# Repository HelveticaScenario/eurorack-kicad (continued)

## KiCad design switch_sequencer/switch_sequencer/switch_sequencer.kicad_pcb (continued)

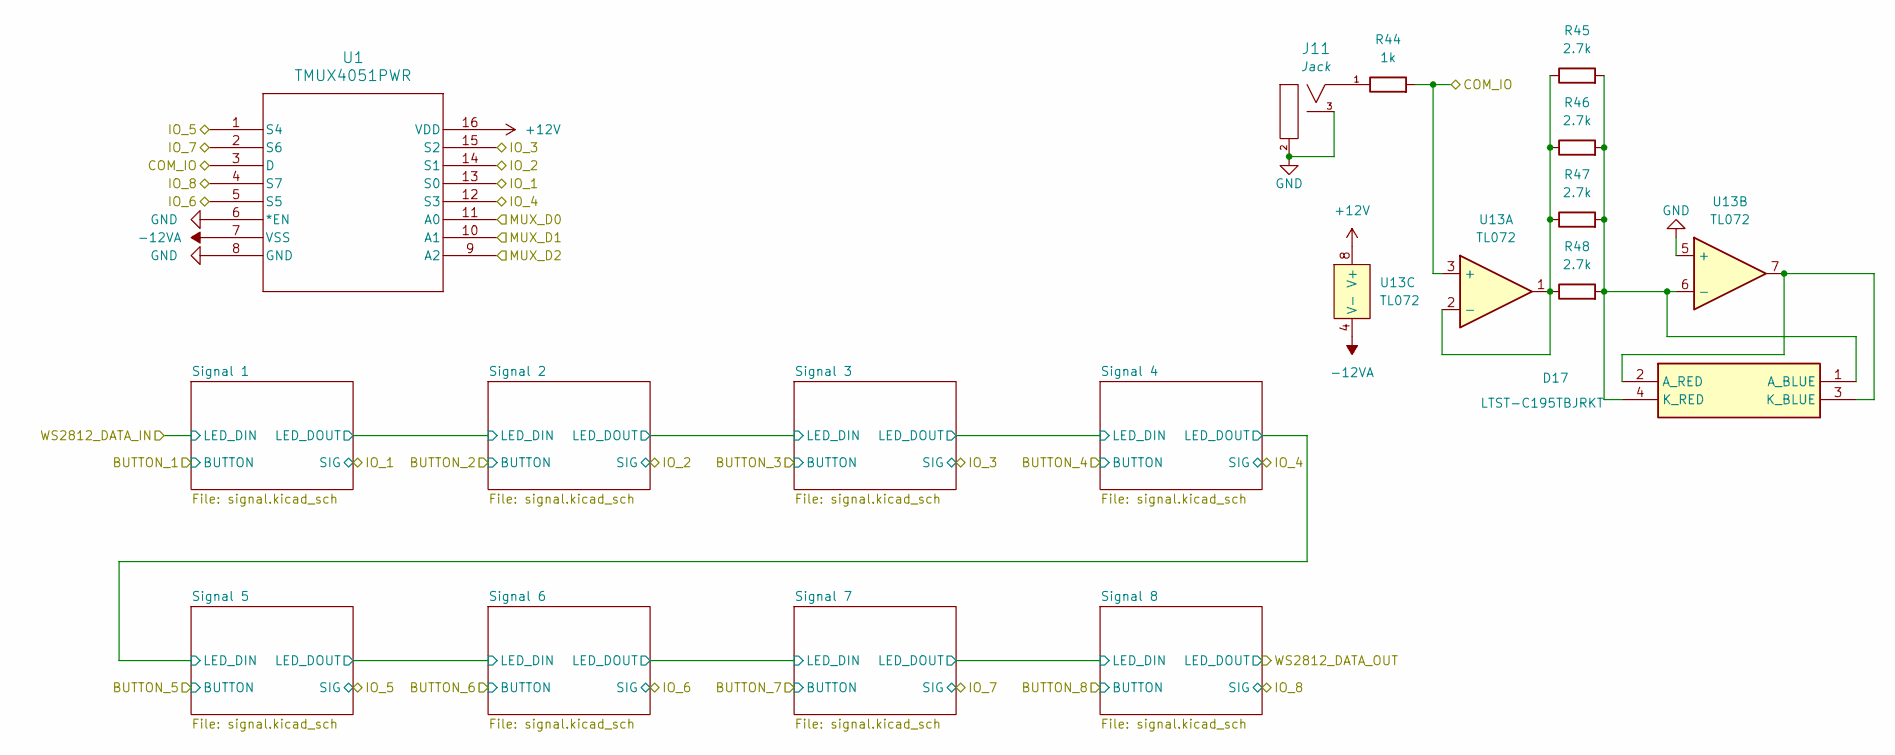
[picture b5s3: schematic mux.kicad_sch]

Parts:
D17: LTST-C195TBJRKT; LTSTC195TBJRKT; Mouser Part Number 859-LTST-C195TBJRKT
J11: 3.5mm_Mono_Switched_sm; EighthInch_PJ398SM; Part Number WQP-WQP518MA
R44: 1k_0402; R_0402; Part Number RC0402FR-071KL; JLCPCB ID C106235
R45, R46, R47, R48: 2.7k_0603; R_0603; Part Number RC0603FR-072K7L; JLCPCB ID C13167
U1: TMUX4051PWR; TSSOP16_PW_TEX
U13: TL072; TSSOP-8_4.4x3mm_Pitch0.65mm; JLCPCB ID C90748

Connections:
+12V: U1.16 (VDD), U13.8 (V+); also elsewhere on the board
-12VA: U1.7 (VSS), U13.4 (V-); also elsewhere on the board
/Mux/COM_IO: R44.2, U1.3 (D), U13.3 (+)
/Mux/IO_1: U1.13 (S0); also elsewhere on the board
/Mux/IO_2: U1.14 (S1); also elsewhere on the board
/Mux/IO_3: U1.15 (S2); also elsewhere on the board
/Mux/IO_4: U1.12 (S3); also elsewhere on the board
/Mux/IO_5: U1.1 (S4); also elsewhere on the board
/Mux/IO_6: U1.5 (S5); also elsewhere on the board
/Mux/IO_7: U1.2 (S6); also elsewhere on the board
/Mux/IO_8: U1.4 (S7); also elsewhere on the board
GND: J11.2 (SHEILD), J11.3 (SW), U1.6 (*EN), U1.8 (GND), U13.5 (+); also elsewhere on the board
MUX_D0: U1.11 (A0); also elsewhere on the board
MUX_D1: U1.10 (A1); also elsewhere on the board
MUX_D2: U1.9 (A2); also elsewhere on the board
unnamed: D17.1 (A_BLUE), D17.4 (K_RED), R45.2, R46.2, R47.2, R48.2, U13.6 (-)
unnamed: D17.2 (A_RED), D17.3 (K_BLUE), U13.7
unnamed: J11.1 (SIG), R44.1
unnamed: R45.1, R46.1, R47.1, R48.1, U13.1, U13.2 (-)

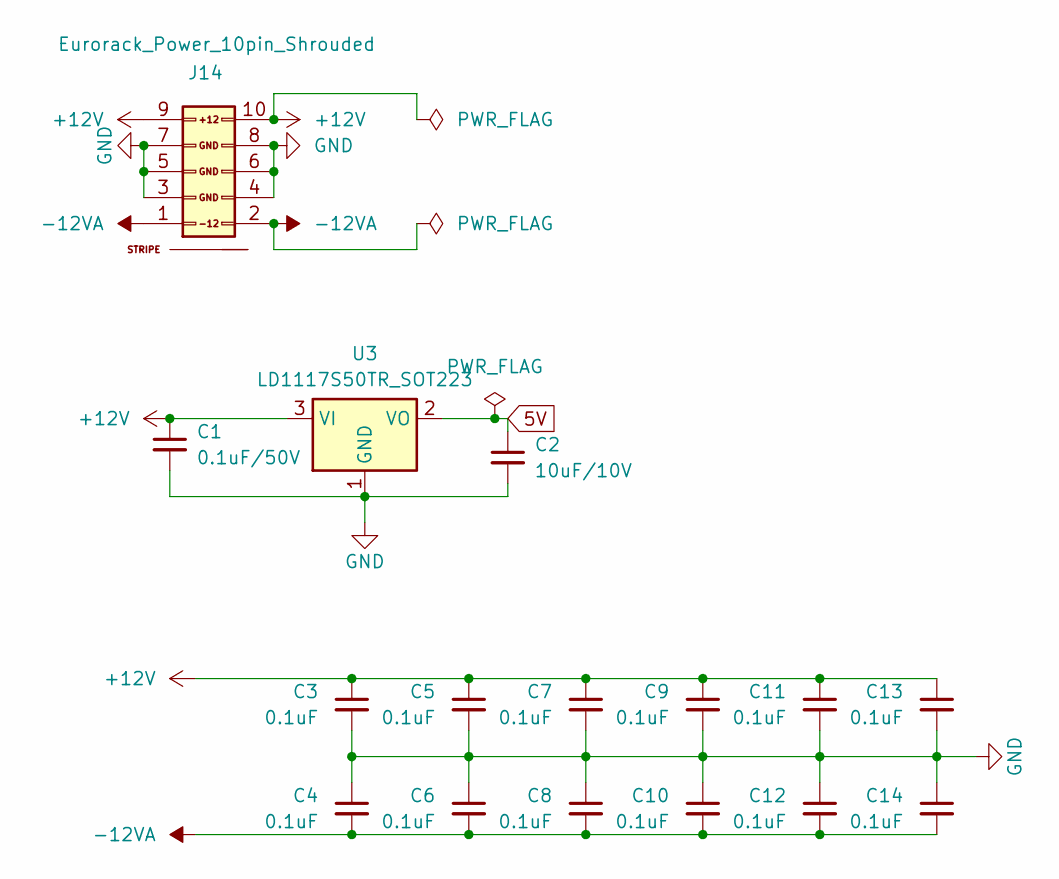
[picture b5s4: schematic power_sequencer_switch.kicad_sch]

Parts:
C1: 0.1uF_0805_50V; C_0805; Part Number GCJ21BL81H104KA01L
C2: 10uF_0603_10V; C_0603; Part Number GRM188R61A106KE69D; JLCPCB ID C19702
C3, C4, C5, C6, C7, C8, C9, C10, C11, C12, C13, C14: 0.1uF_0603_16V; C_0603; Part Number 0603YC104KAT2A; JLCPCB ID C14663
J14: Eurorack_Power_10pin_Shrouded; Pins_2x05_2.54mm_TH_EurorackPower_Shrouded; Part Number 61201021621
U3: LD1117S50TR_SOT223; SOT-223-3_TabPin2

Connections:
5V: C2.1, U3.2 (VO); also elsewhere on the board
+12V: C1.1, C3.1, C5.1, C7.1, C9.1, C11.1, C13.1, J14.9 (+12V), J14.10 (+12V), U3.3 (VI); also elsewhere on the board
-12VA: C4.2, C6.2, C8.2, C10.2, C12.2, C14.2, J14.1 (-12V), J14.2 (-12V); also elsewhere on the board
GND: C1.2, C2.2, C3.2, C4.1, C5.2, C6.1, C7.2, C8.1, C9.2, C10.1, C11.2, C12.1, C13.2, C14.1, J14.3 (GND), J14.4 (GND), J14.5 (GND), J14.6 (GND), J14.7 (GND), J14.8 (GND), U3.1 (GND); also elsewhere on the board

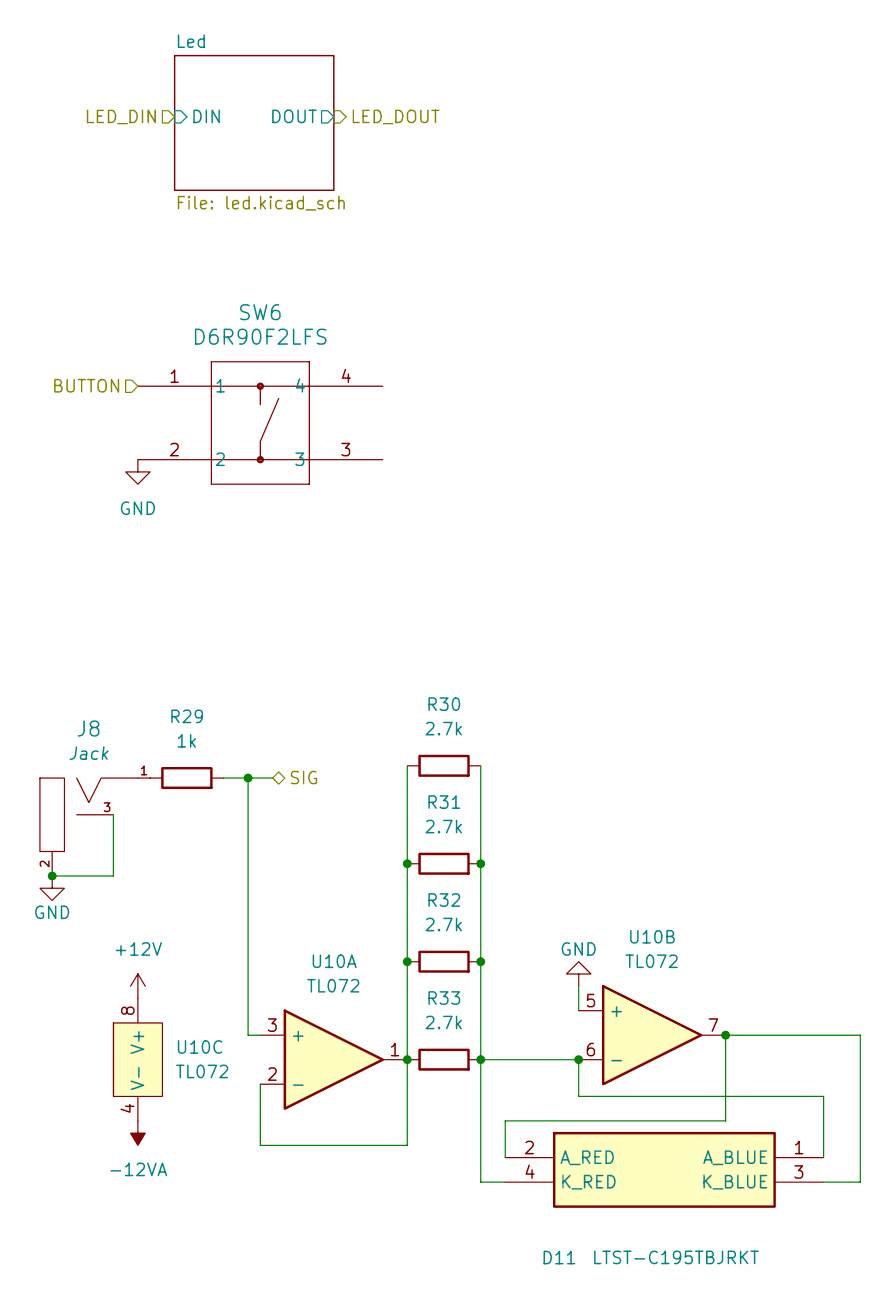
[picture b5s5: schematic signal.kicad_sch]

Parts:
D11: LTST-C195TBJRKT; LTSTC195TBJRKT; Mouser Part Number 859-LTST-C195TBJRKT
J8: 3.5mm_Mono_Switched_sm; EighthInch_PJ398SM; Part Number WQP-WQP518MA
R29: 1k_0402; R_0402; Part Number RC0402FR-071KL; JLCPCB ID C106235
R30, R31, R32, R33: 2.7k_0603; R_0603; Part Number RC0603FR-072K7L; JLCPCB ID C13167
SW6: D6R90F2LFS; D6R90_CNK
U10: TL072; TSSOP-8_4.4x3mm_Pitch0.65mm; JLCPCB ID C90748

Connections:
+12V: U10.8 (V+); also elsewhere on the board
-12VA: U10.4 (V-); also elsewhere on the board
/Mux/IO_6: R29.2, U10.3 (+); also elsewhere on the board
BUTTON_6: SW6.1; also elsewhere on the board
GND: J8.2 (SHEILD), J8.3 (SW), SW6.2, U10.5 (+); also elsewhere on the board
unnamed: D11.1 (A_BLUE), D11.4 (K_RED), R30.2, R31.2, R32.2, R33.2, U10.6 (-)
unnamed: D11.2 (A_RED), D11.3 (K_BLUE), U10.7
unnamed: J8.1 (SIG), R29.1
unnamed: R30.1, R31.1, R32.1, R33.1, U10.1, U10.2 (-)

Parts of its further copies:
D1, D3, D5, D7, D9, D13, D15: LTST-C195TBJRKT; LTSTC195TBJRKT; Mouser Part Number 859-LTST-C195TBJRKT
J3, J4, J5, J6, J7, J9, J10: 3.5mm_Mono_Switched_sm; EighthInch_PJ398SM; Part Number WQP-WQP518MA
R4, R9, R14, R19, R24, R34, R39: 1k_0402; R_0402; Part Number RC0402FR-071KL; JLCPCB ID C106235
R5, R6, R7, R8, R10, R11, R12, R13, R15, R16, R17, R18, R20, R21, R22, R23, R25, R26, R27, R28, R35, R36, R37, R38, R40, R41, R42, R43: 2.7k_0603; R_0603; Part Number RC0603FR-072K7L; JLCPCB ID C13167
SW1, SW2, SW3, SW4, SW5, SW7, SW8: D6R90F2LFS; D6R90_CNK
U5, U6, U7, U8, U9, U11, U12: TL072; TSSOP-8_4.4x3mm_Pitch0.65mm; JLCPCB ID C90748

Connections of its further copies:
+12V: U5.8 (V+), U6.8 (V+), U7.8 (V+), U8.8 (V+), U9.8 (V+), U11.8 (V+), U12.8 (V+); also elsewhere on the board
-12VA: U5.4 (V-), U6.4 (V-), U7.4 (V-), U8.4 (V-), U9.4 (V-), U11.4 (V-), U12.4 (V-); also elsewhere on the board
/Mux/IO_1: R4.2, U5.3 (+); also elsewhere on the board
/Mux/IO_2: R9.2, U6.3 (+); also elsewhere on the board
/Mux/IO_3: R14.2, U7.3 (+); also elsewhere on the board
/Mux/IO_4: R19.2, U8.3 (+); also elsewhere on the board
/Mux/IO_5: R24.2, U9.3 (+); also elsewhere on the board
/Mux/IO_7: R34.2, U11.3 (+); also elsewhere on the board
/Mux/IO_8: R39.2, U12.3 (+); also elsewhere on the board
BUTTON_1: SW1.1; also elsewhere on the board
BUTTON_2: SW2.1; also elsewhere on the board
BUTTON_3: SW3.1; also elsewhere on the board
BUTTON_4: SW4.1; also elsewhere on the board
BUTTON_5: SW5.1; also elsewhere on the board
BUTTON_7: SW7.1; also elsewhere on the board
BUTTON_8: SW8.1; also elsewhere on the board
GND: J3.2 (SHEILD), J3.3 (SW), J4.2 (SHEILD), J4.3 (SW), J5.2 (SHEILD), J5.3 (SW), J6.2 (SHEILD), J6.3 (SW), J7.2 (SHEILD), J7.3 (SW), J9.2 (SHEILD), J9.3 (SW), J10.2 (SHEILD), J10.3 (SW), SW1.2, SW2.2, SW3.2, SW4.2, SW5.2, SW7.2, SW8.2, U5.5 (+), U6.5 (+), U7.5 (+), U8.5 (+), U9.5 (+), U11.5 (+), U12.5 (+); also elsewhere on the board
unnamed: D1.1 (A_BLUE), D1.4 (K_RED), R5.2, R6.2, R7.2, R8.2, U5.6 (-)
unnamed: D1.2 (A_RED), D1.3 (K_BLUE), U5.7
unnamed: D3.1 (A_BLUE), D3.4 (K_RED), R10.2, R11.2, R12.2, R13.2, U6.6 (-)
unnamed: D3.2 (A_RED), D3.3 (K_BLUE), U6.7
unnamed: D5.1 (A_BLUE), D5.4 (K_RED), R15.2, R16.2, R17.2, R18.2, U7.6 (-)
unnamed: D5.2 (A_RED), D5.3 (K_BLUE), U7.7
unnamed: D7.1 (A_BLUE), D7.4 (K_RED), R20.2, R21.2, R22.2, R23.2, U8.6 (-)
unnamed: D7.2 (A_RED), D7.3 (K_BLUE), U8.7
unnamed: D9.1 (A_BLUE), D9.4 (K_RED), R25.2, R26.2, R27.2, R28.2, U9.6 (-)
unnamed: D9.2 (A_RED), D9.3 (K_BLUE), U9.7
unnamed: D13.1 (A_BLUE), D13.4 (K_RED), R35.2, R36.2, R37.2, R38.2, U11.6 (-)
unnamed: D13.2 (A_RED), D13.3 (K_BLUE), U11.7
unnamed: D15.1 (A_BLUE), D15.4 (K_RED), R40.2, R41.2, R42.2, R43.2, U12.6 (-)
unnamed: D15.2 (A_RED), D15.3 (K_BLUE), U12.7
unnamed: J3.1 (SIG), R4.1
unnamed: J4.1 (SIG), R9.1
unnamed: J5.1 (SIG), R14.1
unnamed: J6.1 (SIG), R19.1
unnamed: J7.1 (SIG), R24.1
unnamed: J9.1 (SIG), R34.1
unnamed: J10.1 (SIG), R39.1
unnamed: R5.1, R6.1, R7.1, R8.1, U5.1, U5.2 (-)
unnamed: R10.1, R11.1, R12.1, R13.1, U6.1, U6.2 (-)
unnamed: R15.1, R16.1, R17.1, R18.1, U7.1, U7.2 (-)
unnamed: R20.1, R21.1, R22.1, R23.1, U8.1, U8.2 (-)
unnamed: R25.1, R26.1, R27.1, R28.1, U9.1, U9.2 (-)
unnamed: R35.1, R36.1, R37.1, R38.1, U11.1, U11.2 (-)
unnamed: R40.1, R41.1, R42.1, R43.1, U12.1, U12.2 (-)

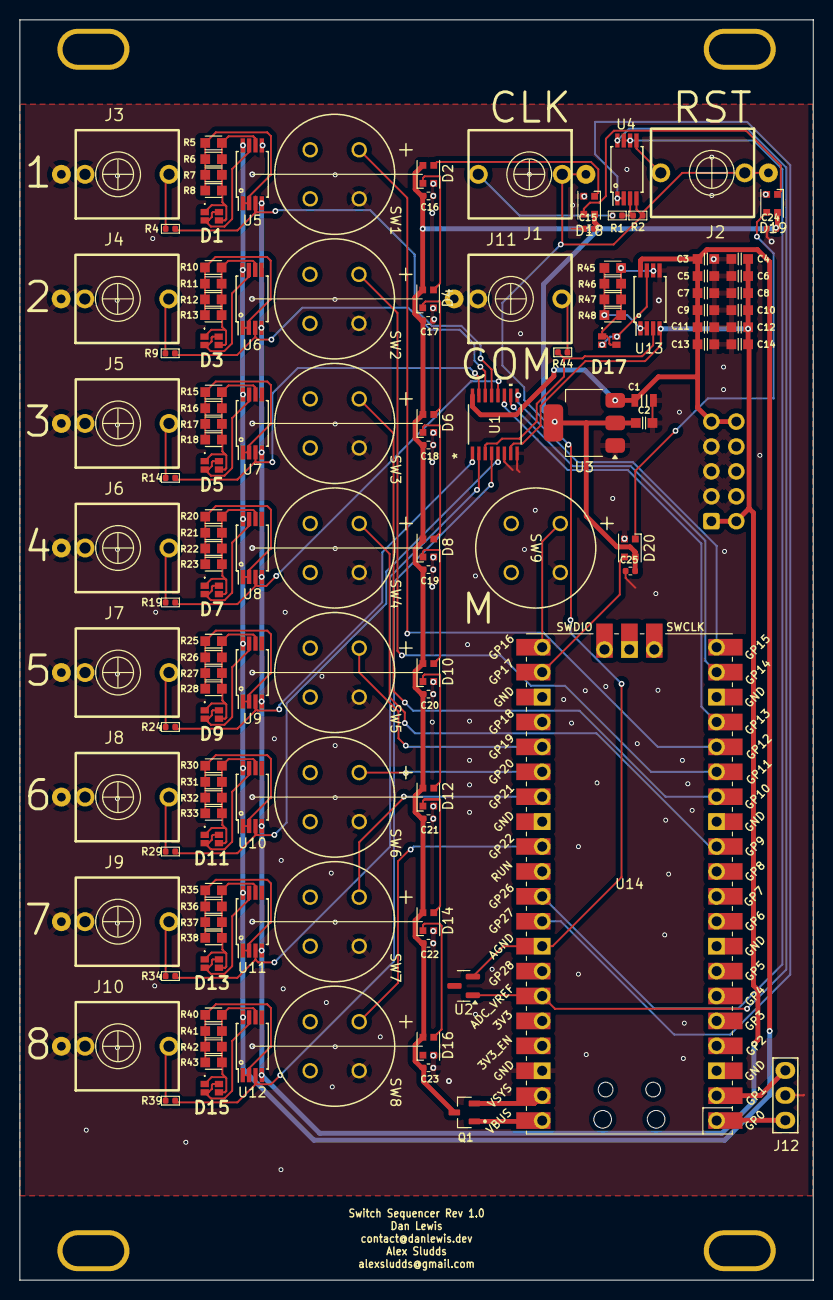
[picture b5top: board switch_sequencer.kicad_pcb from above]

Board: 2 copper layers, 80.9 x 128.5 mm, 133 parts (1 on the bottom side), 83 nets.

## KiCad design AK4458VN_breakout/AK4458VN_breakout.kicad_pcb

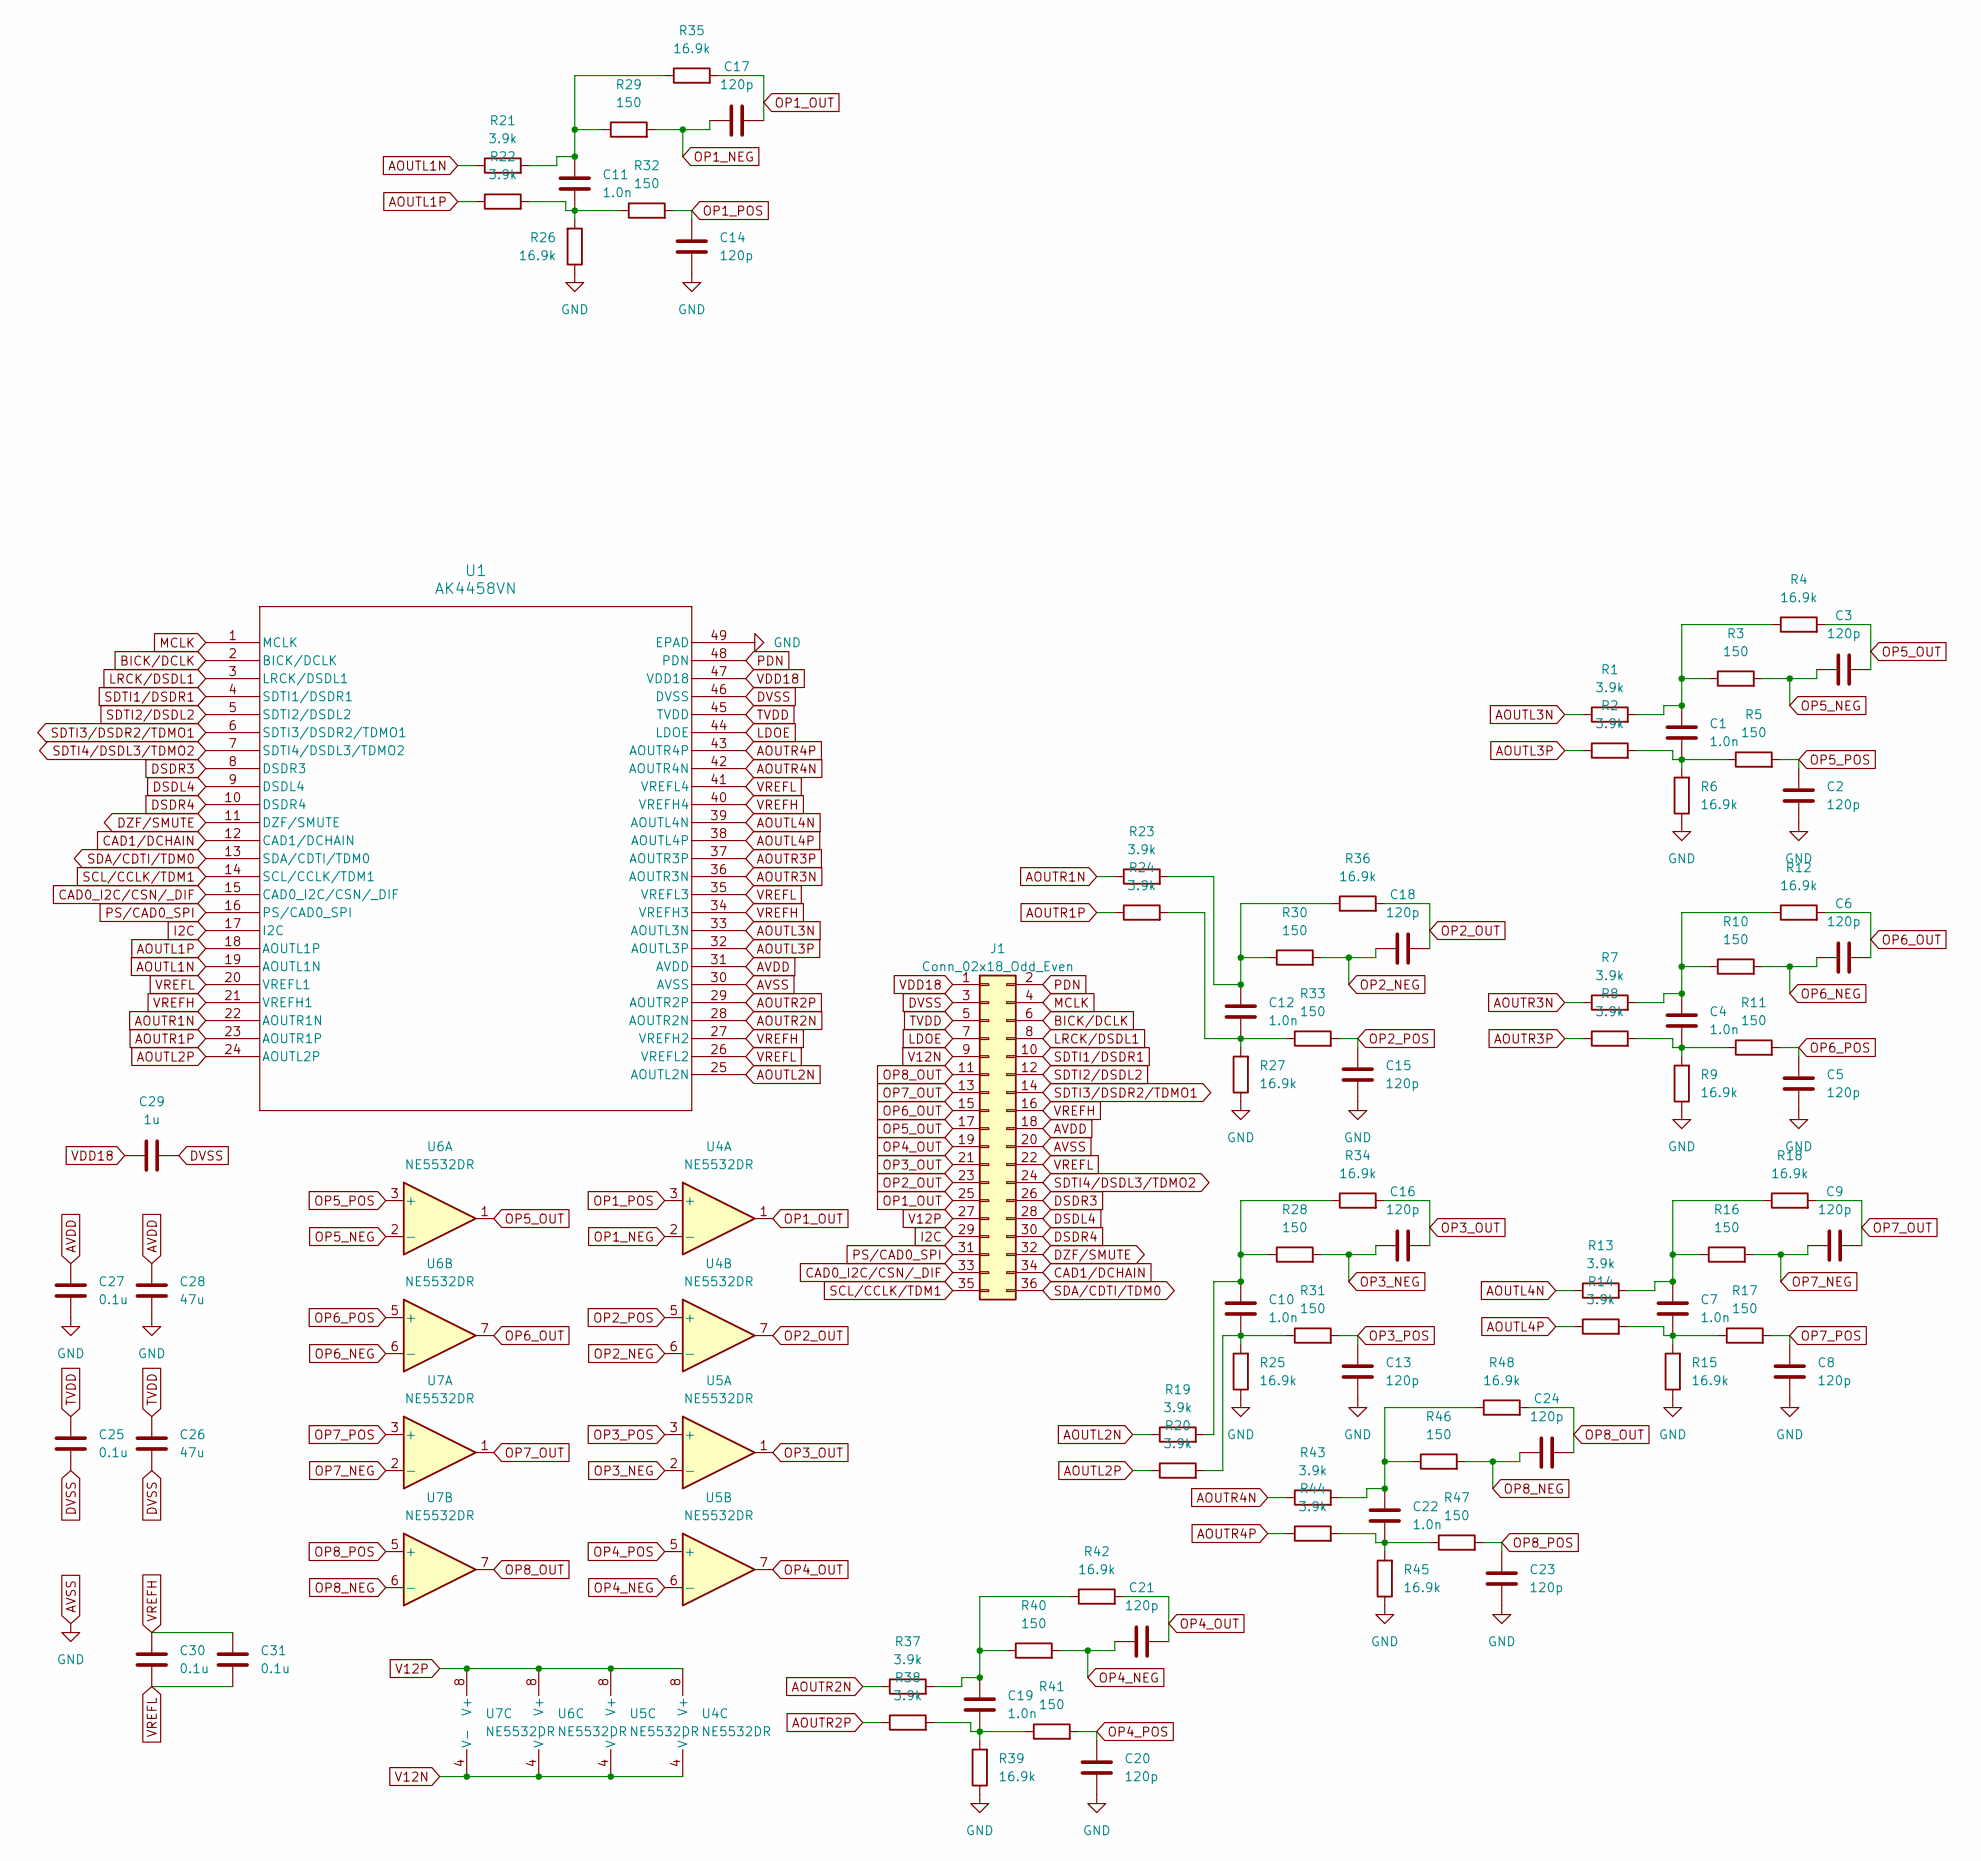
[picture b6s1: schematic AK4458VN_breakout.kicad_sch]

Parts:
C1, C4, C7, C10, C11, C12, C19, C22: 1.0n; C_0805_2012Metric
C2, C3, C5, C6, C8, C9, C13, C14, C15, C16, C17, C18, C20, C21, C23, C24: 120p; C_0603_1608Metric
C25, C27: 0.1u; C_0805_2012Metric
C26, C28: 47u; C_0805_2012Metric
C29: 1u; C_0805_2012Metric
C30, C31: 0.1u; C_0603_1608Metric
J1: Conn_02x18_Odd_Even; PinHeader_2x18_P2.54mm_Vertical
R1, R2, R7, R8, R13, R14, R19, R20, R21, R22, R23, R24, R37, R38, R43, R44: 3.9k; R_0805_2012Metric
R3, R5, R10, R11, R16, R17, R28, R29, R30, R31, R32, R33, R40, R41, R46, R47: 150; R_0805_2012Metric
R4, R6, R9, R12, R15, R18, R25, R26, R27, R34, R35, R36, R39, R42, R45, R48: 16.9k; R_0805_2012Metric
U1: AK4458VN; QFN48_7x7-0p5_AKM
U4, U5, U6, U7: NE5532DR; SOIC127P599X175-8N

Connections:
AOUTL1N: R21.1, U1.19 (AOUTL1N)
AOUTL1P: R22.1, U1.18 (AOUTL1P)
AOUTL2N: R19.1, U1.25 (AOUTL2N)
AOUTL2P: R20.1, U1.24 (AOUTL2P)
AOUTL3N: R1.1, U1.33 (AOUTL3N)
AOUTL3P: R2.1, U1.32 (AOUTL3P)
AOUTL4N: R13.1, U1.39 (AOUTL4N)
AOUTL4P: R14.1, U1.38 (AOUTL4P)
AOUTR1N: R23.1, U1.22 (AOUTR1N)
AOUTR1P: R24.1, U1.23 (AOUTR1P)
AOUTR2N: R37.1, U1.28 (AOUTR2N)
AOUTR2P: R38.1, U1.29 (AOUTR2P)
AOUTR3N: R7.1, U1.36 (AOUTR3N)
AOUTR3P: R8.1, U1.37 (AOUTR3P)
AOUTR4N: R43.1, U1.42 (AOUTR4N)
AOUTR4P: R44.1, U1.43 (AOUTR4P)
AVDD: C27.1, C28.1, J1.18, U1.31 (AVDD)
AVSS: C2.2, C5.2, C8.2, C13.2, C14.2, C15.2, C20.2, C23.2, C27.2, C28.2, J1.20, R6.1, R9.1, R15.1, R25.1, R26.1, R27.1, R39.1, R45.1, U1.30 (AVSS), U1.49 (EPAD)
BICK/DCLK: J1.6, U1.2 (BICK/DCLK)
CAD0_I2C/CSN/_DIF: J1.33, U1.15 (CAD0_I2C/CSN/_DIF)
CAD1/DCHAIN: J1.34, U1.12 (CAD1/DCHAIN)
DSDL4: J1.28, U1.9 (DSDL4)
DSDR3: J1.26, U1.8 (DSDR3)
DSDR4: J1.30, U1.10 (DSDR4)
DVSS: C25.2, C26.2, C29.2, J1.3, U1.46 (DVSS)
DZF/SMUTE: J1.32, U1.11 (DZF/SMUTE)
I2C: J1.29, U1.17 (I2C)
LDOE: J1.7, U1.44 (LDOE)
LRCK/DSDL1: J1.8, U1.3 (LRCK/DSDL1)
MCLK: J1.4, U1.1 (MCLK)
unnamed: C1.1, R1.2, R3.1, R4.1
unnamed: C1.2, R2.2, R5.1, R6.2
unnamed: C4.1, R7.2, R10.1, R12.1
unnamed: C4.2, R8.2, R9.2, R11.1
unnamed: C7.1, R13.2, R16.1, R18.1
unnamed: C7.2, R14.2, R15.2, R17.1
unnamed: C10.1, R19.2, R28.1, R34.1
unnamed: C10.2, R20.2, R25.2, R31.1
unnamed: C11.1, R21.2, R29.1, R35.1
unnamed: C11.2, R22.2, R26.2, R32.1
unnamed: C12.1, R23.2, R30.1, R36.1
unnamed: C12.2, R24.2, R27.2, R33.1
unnamed: C19.1, R37.2, R40.1, R42.1
unnamed: C19.2, R38.2, R39.2, R41.1
unnamed: C22.1, R43.2, R46.1, R48.1
unnamed: C22.2, R44.2, R45.2, R47.1
OP1_NEG: C17.1, R29.2, U4.2 (-)
OP1_OUT: C17.2, J1.25, R35.2, U4.1
OP1_POS: C14.1, R32.2, U4.3 (+)
OP2_NEG: C18.1, R30.2, U4.6 (-)
OP2_OUT: C18.2, J1.23, R36.2, U4.7
OP2_POS: C15.1, R33.2, U4.5 (+)
OP3_NEG: C16.1, R28.2, U5.2 (-)
OP3_OUT: C16.2, J1.21, R34.2, U5.1
OP3_POS: C13.1, R31.2, U5.3 (+)
OP4_NEG: C21.1, R40.2, U5.6 (-)
OP4_OUT: C21.2, J1.19, R42.2, U5.7
OP4_POS: C20.1, R41.2, U5.5 (+)
OP5_NEG: C3.1, R3.2, U6.2 (-)
OP5_OUT: C3.2, J1.17, R4.2, U6.1
OP5_POS: C2.1, R5.2, U6.3 (+)
OP6_NEG: C6.1, R10.2, U6.6 (-)
OP6_OUT: C6.2, J1.15, R12.2, U6.7
OP6_POS: C5.1, R11.2, U6.5 (+)
OP7_NEG: C9.1, R16.2, U7.2 (-)
OP7_OUT: C9.2, J1.13, R18.2, U7.1
OP7_POS: C8.1, R17.2, U7.3 (+)
OP8_NEG: C24.1, R46.2, U7.6 (-)
OP8_OUT: C24.2, J1.11, R48.2, U7.7
OP8_POS: C23.1, R47.2, U7.5 (+)
PDN: J1.2, U1.48 (PDN)
PS/CAD0_SPI: J1.31, U1.16 (PS/CAD0_SPI)
SCL/CCLK/TDM1: J1.35, U1.14 (SCL/CCLK/TDM1)
SDA/CDTI/TDM0: J1.36, U1.13 (SDA/CDTI/TDM0)
SDTI1/DSDR1: J1.10, U1.4 (SDTI1/DSDR1)
SDTI2/DSDL2: J1.12, U1.5 (SDTI2/DSDL2)
SDTI3/DSDR2/TDMO1: J1.14, U1.6 (SDTI3/DSDR2/TDMO1)
SDTI4/DSDL3/TDMO2: J1.24, U1.7 (SDTI4/DSDL3/TDMO2)
TVDD: C25.1, C26.1, J1.5, U1.45 (TVDD)
V12N: J1.9, U4.4 (V-), U5.4 (V-), U6.4 (V-), U7.4 (V-)
V12P: J1.27, U4.8 (V+), U5.8 (V+), U6.8 (V+), U7.8 (V+)
VDD18: C29.1, J1.1, U1.47 (VDD18)
VREFH: C30.1, C31.1, J1.16, U1.21 (VREFH1), U1.27 (VREFH2), U1.34 (VREFH3), U1.40 (VREFH4)
VREFL: C30.2, C31.2, J1.22, U1.20 (VREFL1), U1.26 (VREFL2), U1.35 (VREFL3), U1.41 (VREFL4)

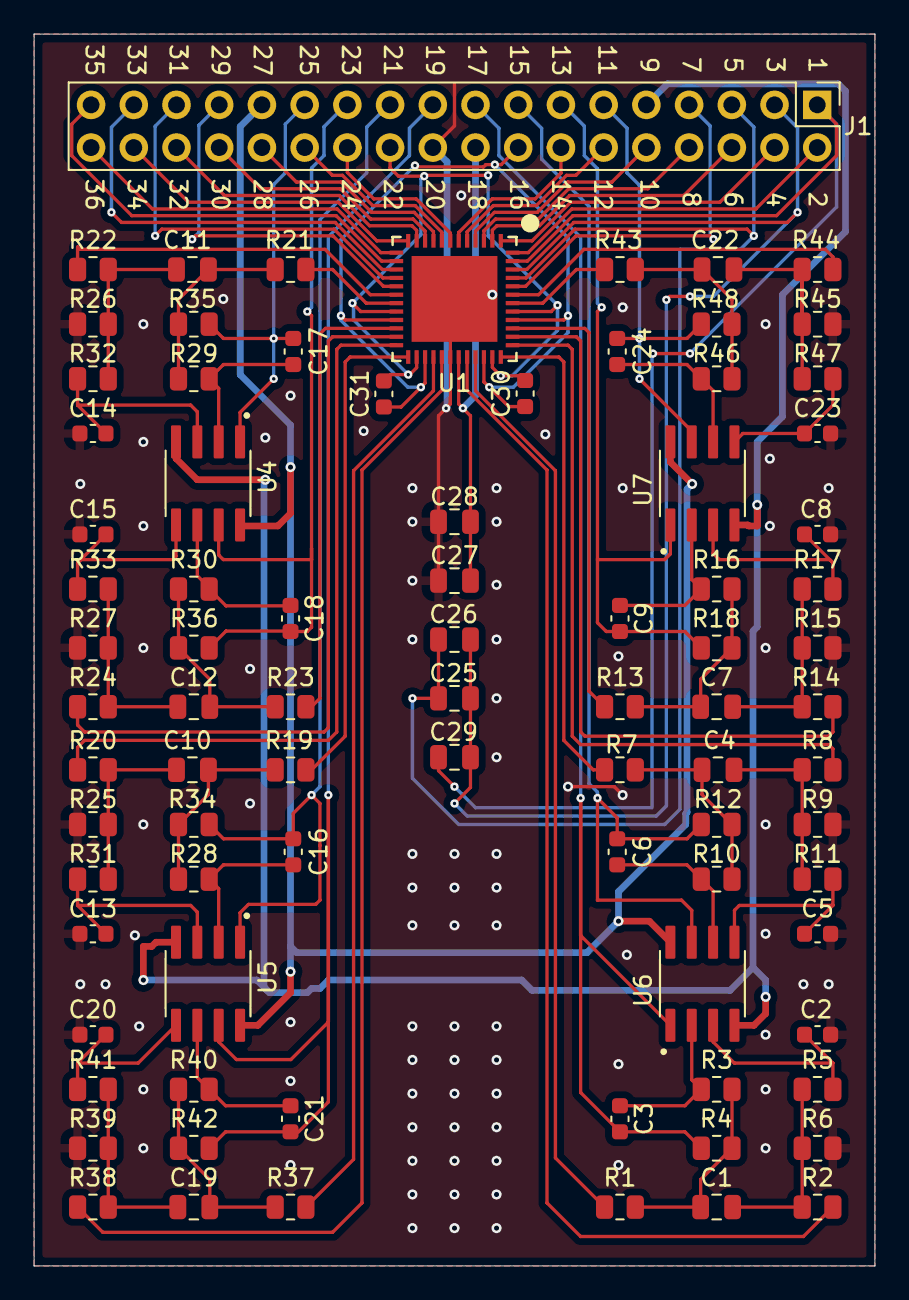
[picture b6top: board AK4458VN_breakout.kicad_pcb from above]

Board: 2 copper layers, 50.0 x 73.2 mm, 85 parts (0 on the bottom side), 84 nets.

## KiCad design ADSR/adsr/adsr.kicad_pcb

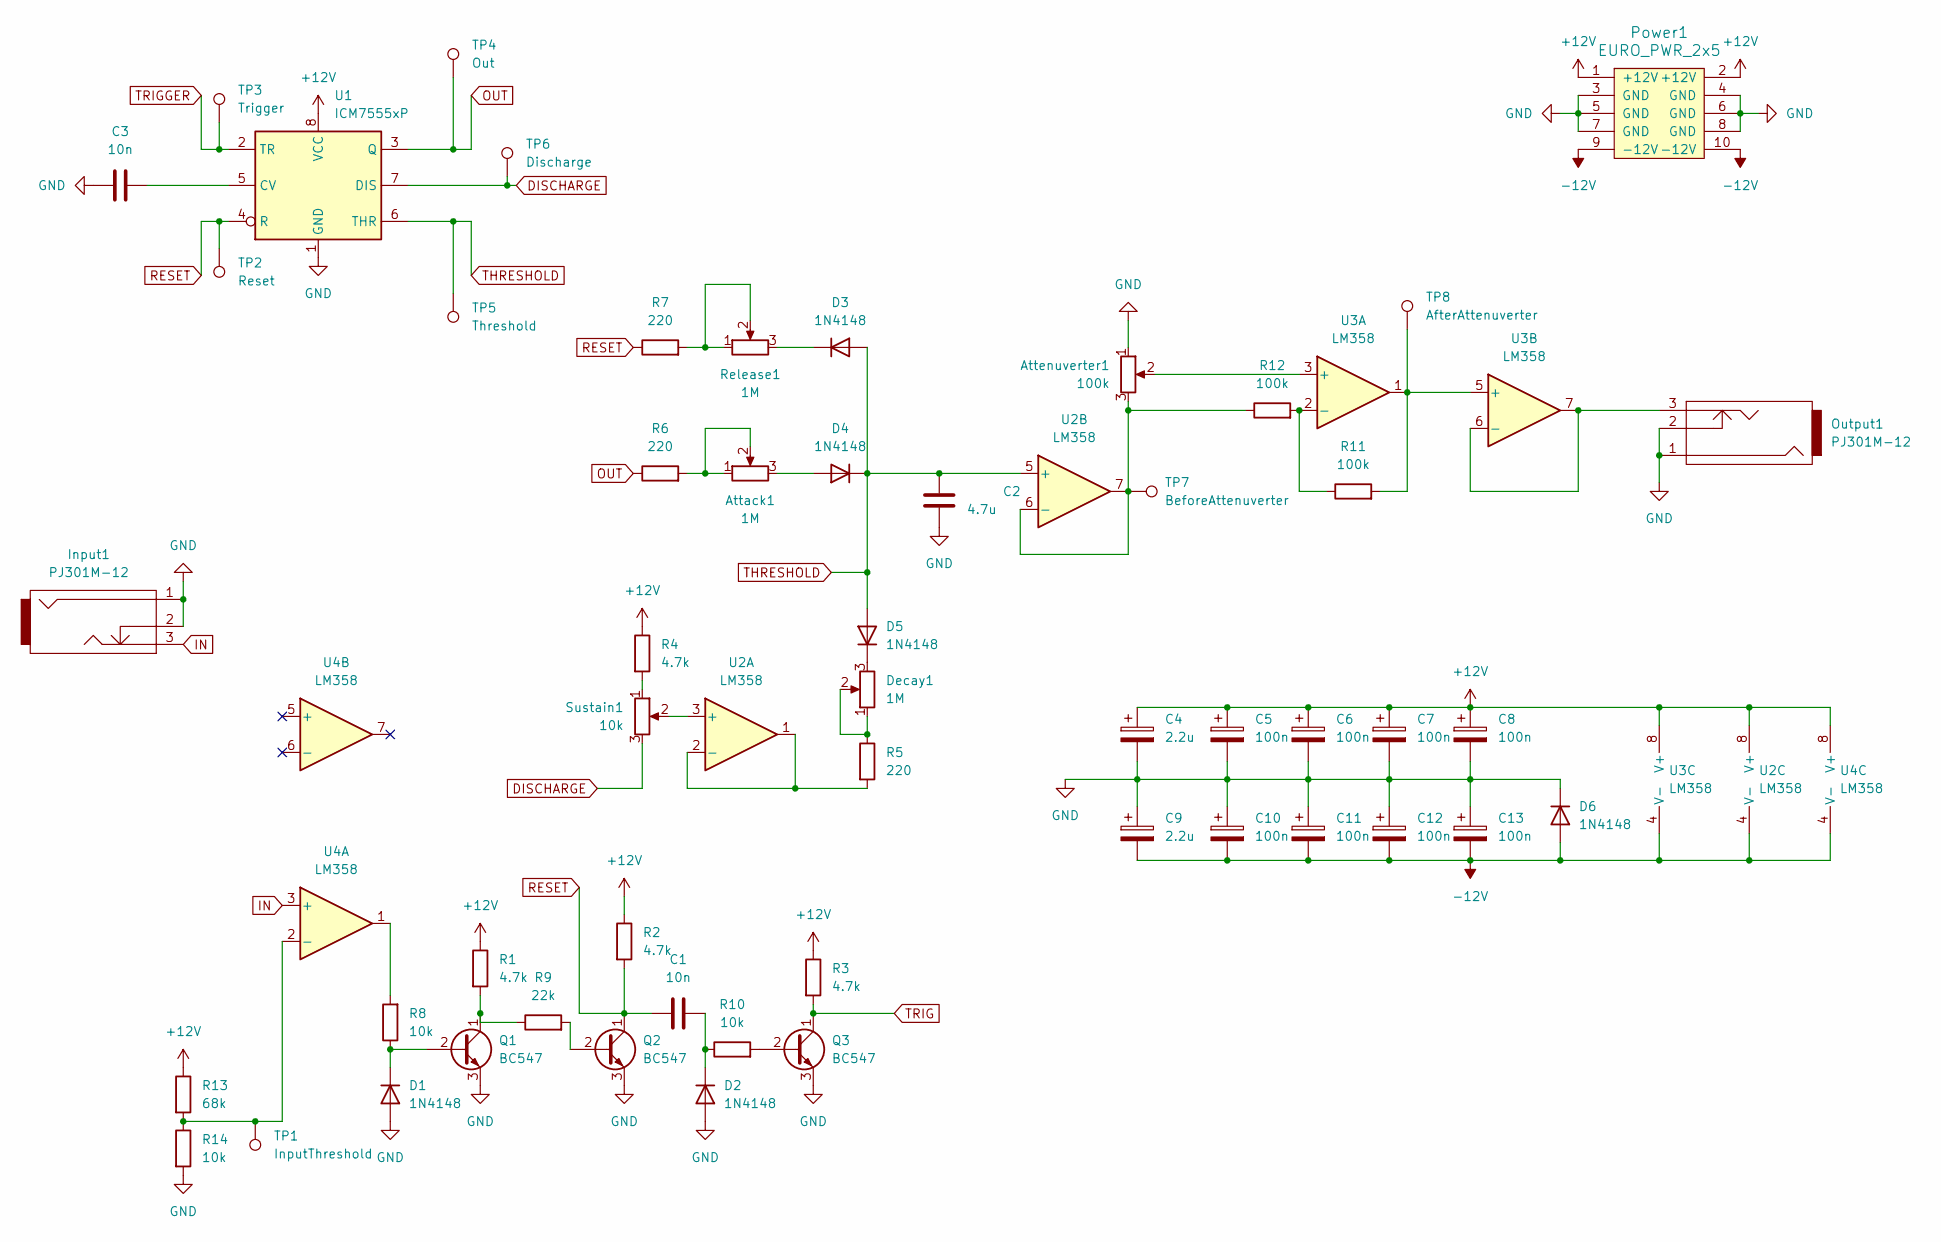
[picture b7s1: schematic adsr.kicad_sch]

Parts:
Attack1: 1M; Alpha9mmPot
Attenuverter1: 100k; Alpha9mmPot
C1, C3: 10n; C_Disc_D5.0mm_W2.5mm_P5.00mm
C2: 4.7u; C_Disc_D5.0mm_W2.5mm_P5.00mm
C4, C9: 2.2u; C_Disc_D5.0mm_W2.5mm_P5.00mm
C5, C6, C7, C8, C10, C11, C12, C13: 100n; C_Disc_D5.0mm_W2.5mm_P5.00mm
D1, D2, D3, D4, D5, D6: 1N4148; D_DO-35_SOD27_P7.62mm_Horizontal
Decay1: 1M; Alpha9mmPot
Input1: PJ301M-12
Output1: PJ301M-12
Power1: EURO_PWR_2x5; PinHeader_2x05_P2.54mm_Vertical
Q1, Q2, Q3: BC547; TO-92_Inline
R1, R2, R3, R4: 4.7k; R_Axial_DIN0207_L6.3mm_D2.5mm_P10.16mm_Horizontal
R5, R6, R7: 220; R_Axial_DIN0207_L6.3mm_D2.5mm_P10.16mm_Horizontal
R8, R10, R14: 10k; R_Axial_DIN0207_L6.3mm_D2.5mm_P10.16mm_Horizontal
R9: 22k; R_Axial_DIN0207_L6.3mm_D2.5mm_P10.16mm_Horizontal
R11, R12: 100k; R_Axial_DIN0207_L6.3mm_D2.5mm_P10.16mm_Horizontal
R13: 68k; R_Axial_DIN0207_L6.3mm_D2.5mm_P10.16mm_Horizontal
Release1: 1M; Alpha9mmPot
Sustain1: 10k; Alpha9mmPot
TP1: InputThreshold; TestPoint_Loop_D2.50mm_Drill1.0mm
TP2: Reset; TestPoint_Loop_D2.50mm_Drill1.0mm
TP3: Trigger; TestPoint_Loop_D2.50mm_Drill1.0mm
TP4: Out; TestPoint_Loop_D2.50mm_Drill1.0mm
TP5: Threshold; TestPoint_Loop_D2.50mm_Drill1.0mm
TP6: Discharge; TestPoint_Loop_D2.50mm_Drill1.0mm
TP7: BeforeAttenuverter; TestPoint_Loop_D2.50mm_Drill1.0mm
TP8: AfterAttenuverter; TestPoint_Loop_D2.50mm_Drill1.0mm
U1: ICM7555xP; DIP-8_W7.62mm
U2, U3, U4: LM358; DIP794W45P254L959H508Q8

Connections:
+12V: C4.1, C5.1, C6.1, C7.1, C8.1, Power1.1 (+12V), Power1.2 (+12V), R1.1, R2.1, R3.1, R4.1, R13.1, U1.8 (VCC), U2.8 (V+), U3.8 (V+), U4.8 (V+)
-12V: C9.2, C10.2, C11.2, C12.2, C13.2, D6.2 (A), Power1.9 (-12V), Power1.10 (-12V), U2.4 (V-), U3.4 (V-), U4.4 (V-)
DISCHARGE: Sustain1.3, TP6.1, U1.7 (DIS)
GND: Attenuverter1.1, C2.1, C3.2, C4.2, C5.2, C6.2, C7.2, C8.2, C9.1, C10.1, C11.1, C12.1, C13.1, D1.2 (A), D2.2 (A), D6.1 (K), Input1.1, Input1.2, Output1.1, Output1.2, Power1.3 (GND), Power1.4 (GND), Power1.5 (GND), Power1.6 (GND), Power1.7 (GND), Power1.8 (GND), Q1.3 (E), Q2.3 (E), Q3.3 (E), R14.2, U1.1 (GND)
IN: Input1.3, U4.3 (+)
unnamed: Attack1.1, Attack1.2, R6.2
unnamed: D1.1 (K), Q1.2 (B), R8.1
unnamed: C1.1, D2.1 (K), R10.1
unnamed: D3.1 (K), Release1.3
unnamed: Attack1.3, D4.2 (A)
unnamed: D5.1 (K), Decay1.3
unnamed: Decay1.1, Decay1.2, R5.1
unnamed: Q1.1 (C), R1.2, R9.1
unnamed: Q2.2 (B), R9.2
unnamed: Q3.2 (B), R10.2
unnamed: R4.2, Sustain1.1
unnamed: R7.2, Release1.1, Release1.2
unnamed: R8.2, U4.1
unnamed: C3.1, U1.5 (CV)
unnamed: Sustain1.2, U2.3 (+)
unnamed: R5.2, U2.1, U2.2 (-)
unnamed: Attenuverter1.3, R12.1, TP7.1, U2.6 (-), U2.7
unnamed: Attenuverter1.2, U3.3 (+)
unnamed: R11.1, R12.2, U3.2 (-)
unnamed: R11.2, TP8.1, U3.1, U3.5 (+)
unnamed: Output1.3, U3.6 (-), U3.7
unnamed: R13.2, R14.1, TP1.1, U4.2 (-)
OUT: R6.1, TP4.1, U1.3 (Q)
RESET: C1.2, Q2.1 (C), R2.2, R7.1, TP2.1, U1.4 (R)
THRESHOLD: C2.2, D3.2 (A), D4.1 (K), D5.2 (A), TP5.1, U1.6 (THR), U2.5 (+)
TRIG: Q3.1 (C), R3.2
TRIGGER: TP3.1, U1.2 (TR)

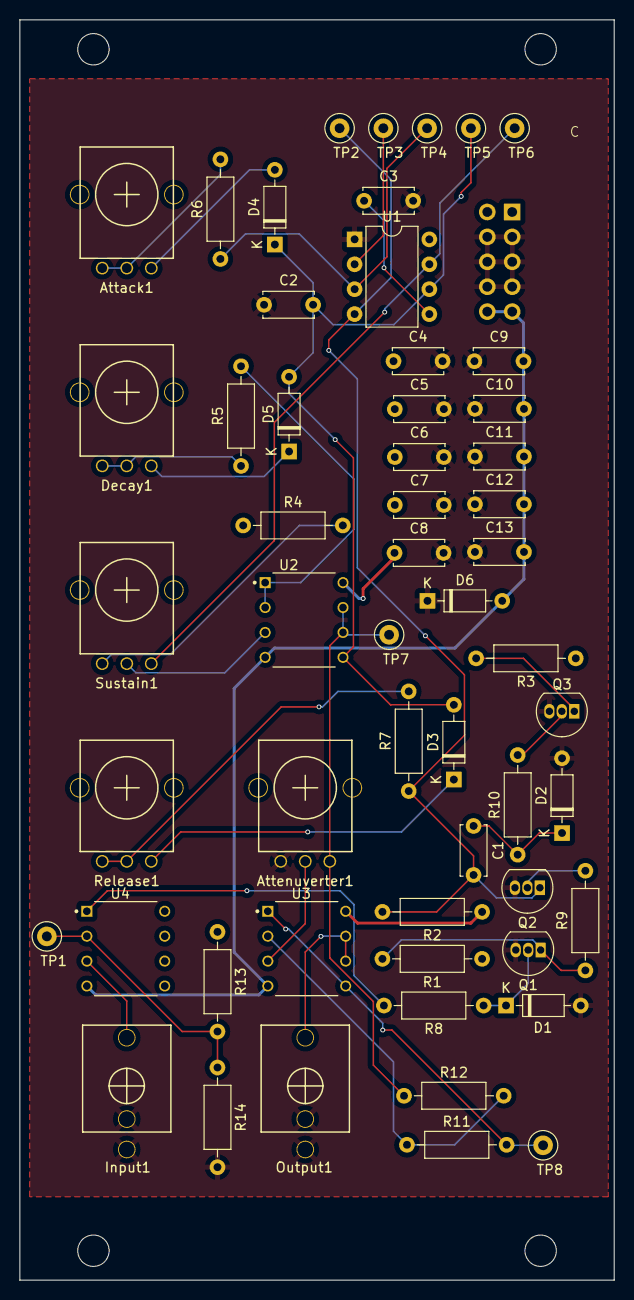
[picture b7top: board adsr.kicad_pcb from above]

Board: 2 copper layers, 60.6 x 128.5 mm, 56 parts (1 on the bottom side), 32 nets.

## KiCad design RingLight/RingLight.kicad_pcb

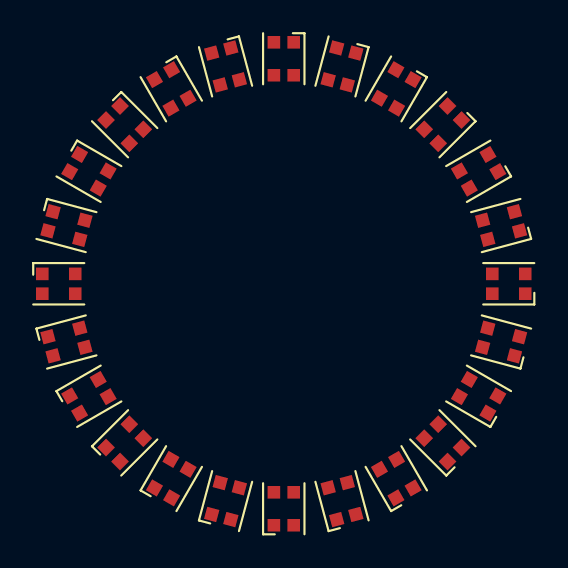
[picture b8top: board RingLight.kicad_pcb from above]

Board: 2 copper layers, 24 parts (0 on the bottom side), 4 nets, no tracks yet.

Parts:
D1, D2, D3, D4, D5, D6, D7, D8, D9, D10, D11, D12, D13, D14, D15, D16, D17, D18, D19, D20, D21, D22, D23, D24: WS2812B-2020; LED_WS2812B-2020_PLCC4_2.0x2.0mm

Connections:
IN: D1.3 (DIN), D2.3 (DIN), D3.3 (DIN), D4.3 (DIN), D5.3 (DIN), D6.3 (DIN), D7.3 (DIN), D8.3 (DIN), D9.3 (DIN), D10.3 (DIN), D11.3 (DIN), D12.3 (DIN), D13.3 (DIN), D14.3 (DIN), D15.3 (DIN), D16.3 (DIN), D17.3 (DIN), D18.3 (DIN), D19.3 (DIN), D20.3 (DIN), D21.3 (DIN), D22.3 (DIN), D23.3 (DIN), D24.3 (DIN)
unnamed: D1.1 (DOUT), D2.1 (DOUT), D3.1 (DOUT), D4.1 (DOUT), D5.1 (DOUT), D6.1 (DOUT), D7.1 (DOUT), D8.1 (DOUT), D9.1 (DOUT), D10.1 (DOUT), D11.1 (DOUT), D12.1 (DOUT), D13.1 (DOUT), D14.1 (DOUT), D15.1 (DOUT), D16.1 (DOUT), D17.1 (DOUT), D18.1 (DOUT), D19.1 (DOUT), D20.1 (DOUT), D21.1 (DOUT), D22.1 (DOUT), D23.1 (DOUT), D24.1 (DOUT)
VDD: D1.4 (VDD), D2.4 (VDD), D3.4 (VDD), D4.4 (VDD), D5.4 (VDD), D6.4 (VDD), D7.4 (VDD), D8.4 (VDD), D9.4 (VDD), D10.4 (VDD), D11.4 (VDD), D12.4 (VDD), D13.4 (VDD), D14.4 (VDD), D15.4 (VDD), D16.4 (VDD), D17.4 (VDD), D18.4 (VDD), D19.4 (VDD), D20.4 (VDD), D21.4 (VDD), D22.4 (VDD), D23.4 (VDD), D24.4 (VDD)
VSS: D1.2 (VSS), D2.2 (VSS), D3.2 (VSS), D4.2 (VSS), D5.2 (VSS), D6.2 (VSS), D7.2 (VSS), D8.2 (VSS), D9.2 (VSS), D10.2 (VSS), D11.2 (VSS), D12.2 (VSS), D13.2 (VSS), D14.2 (VSS), D15.2 (VSS), D16.2 (VSS), D17.2 (VSS), D18.2 (VSS), D19.2 (VSS), D20.2 (VSS), D21.2 (VSS), D22.2 (VSS), D23.2 (VSS), D24.2 (VSS)

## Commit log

2024-08-27 ADSR schematic
2024-08-27 falstad file
2024-08-27 change schematic, add symbols and footprints
2024-10-20 more modules
2024-10-20 ak4458vn breakout v1.1
2024-11-04 pendulum
2024-11-19 teensy interface prototype
2024-11-22 double pendulum 4ms package path update
2024-11-22 teensy to dac connections
2024-11-24 symbols and footprints project relative
2024-11-24 rename some symbols, create switch sequencer
2024-11-25 add updated version of 5v regulator schematic block
2024-11-25 Updated filtering between VREF's. Added separate power supply for Teensy on 5V. Added test points. Added ADC input
2024-11-25 Created first set of DAC outputs layout
2024-11-25 out pairs as pages
2024-11-25 more switch sequencer
2024-11-26 Added layout for power regulators
2024-11-26 Altered ground planes
2024-11-26 connect rest of signal, add joining vias
2024-11-27 Finished core electrical layout
2024-11-27 checks, added silkscreens
2024-11-27 mounting holes
2024-11-29 sizing, remove SW label
2024-11-30 Updated double pendulum with todo notes
2024-11-30 Updated schematic of sample and hold, attenuveters, sequential switch
2024-11-30 Reformated folder structure. Finished layout of sample and hold.
2024-12-01 Added attenuveter PCB
2024-12-02 finish attenuverters, sample and hold
2024-12-02 Added push button
2024-12-02 Generated gerbers for boards
2024-12-02 sequential switch wip
2024-12-03 sequential swtich more wip
2024-12-03 Finished schematic and layout of the double pendulum
2024-12-03 sequential switch wip more more
2024-12-04 sequential switch finished
2024-12-05 Added label to switch sequencer
2025-01-20 dc interface
2025-01-20 double pendulum
2025-01-20 attenuverters
2025-01-20 sample and hold
2025-01-20 switch sequencer
2025-01-20 switch sequencer code
2025-02-16 it works
